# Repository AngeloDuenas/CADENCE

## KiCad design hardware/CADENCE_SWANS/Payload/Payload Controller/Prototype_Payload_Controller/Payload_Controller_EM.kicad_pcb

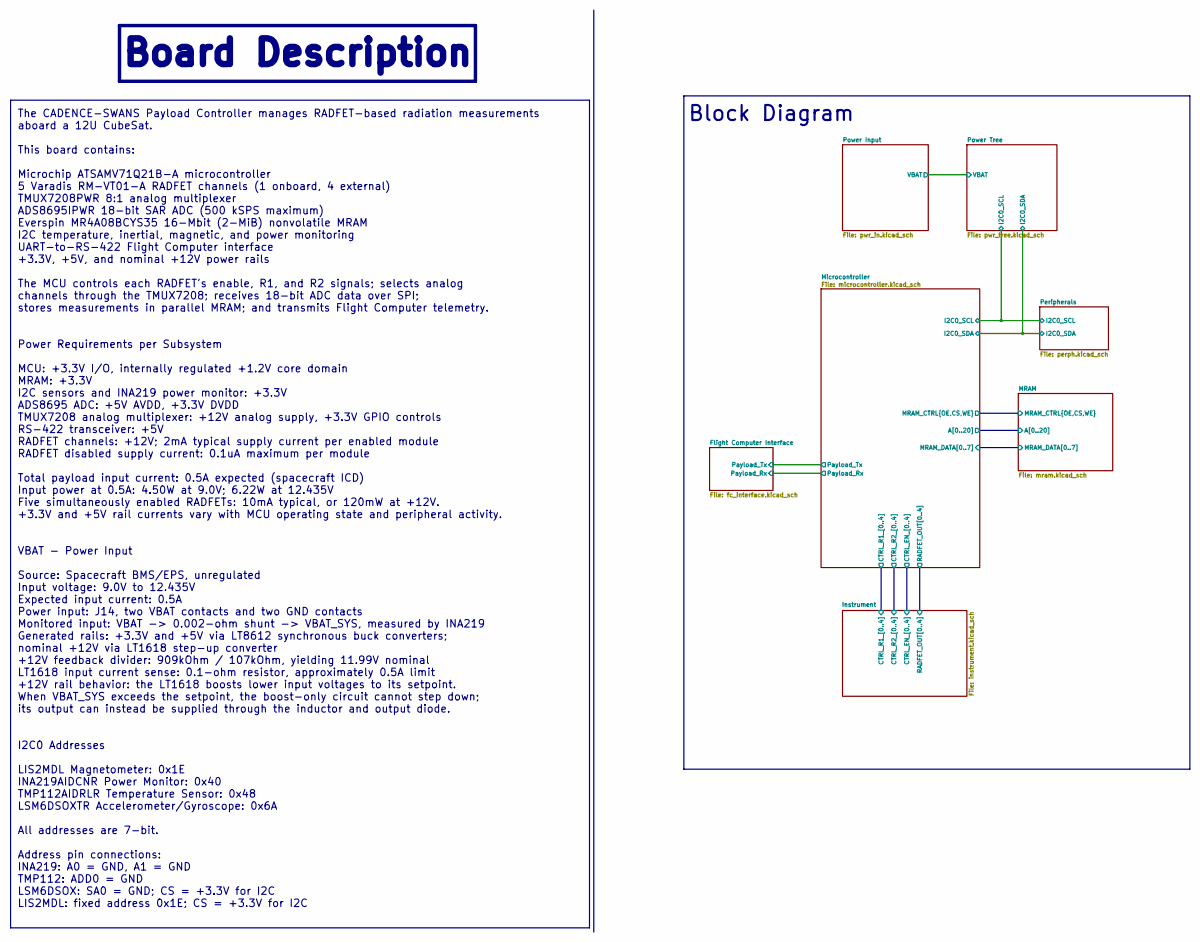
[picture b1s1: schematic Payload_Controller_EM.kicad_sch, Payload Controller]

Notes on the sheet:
Board Description
Block Diagram
The CADENCE-SWANS Payload Controller manages RADFET-based radiation measurements aboard a 12U CubeSat. This board contains: Microchip ATSAMV71Q21B-A microcontroller 5 Varadis RM-VT01-A RADFET channels (1 onboard, 4 external) TMUX7208PWR 8:1 analog multiplexer ADS8695IPWR 18-bit SAR ADC (500 kSPS ma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

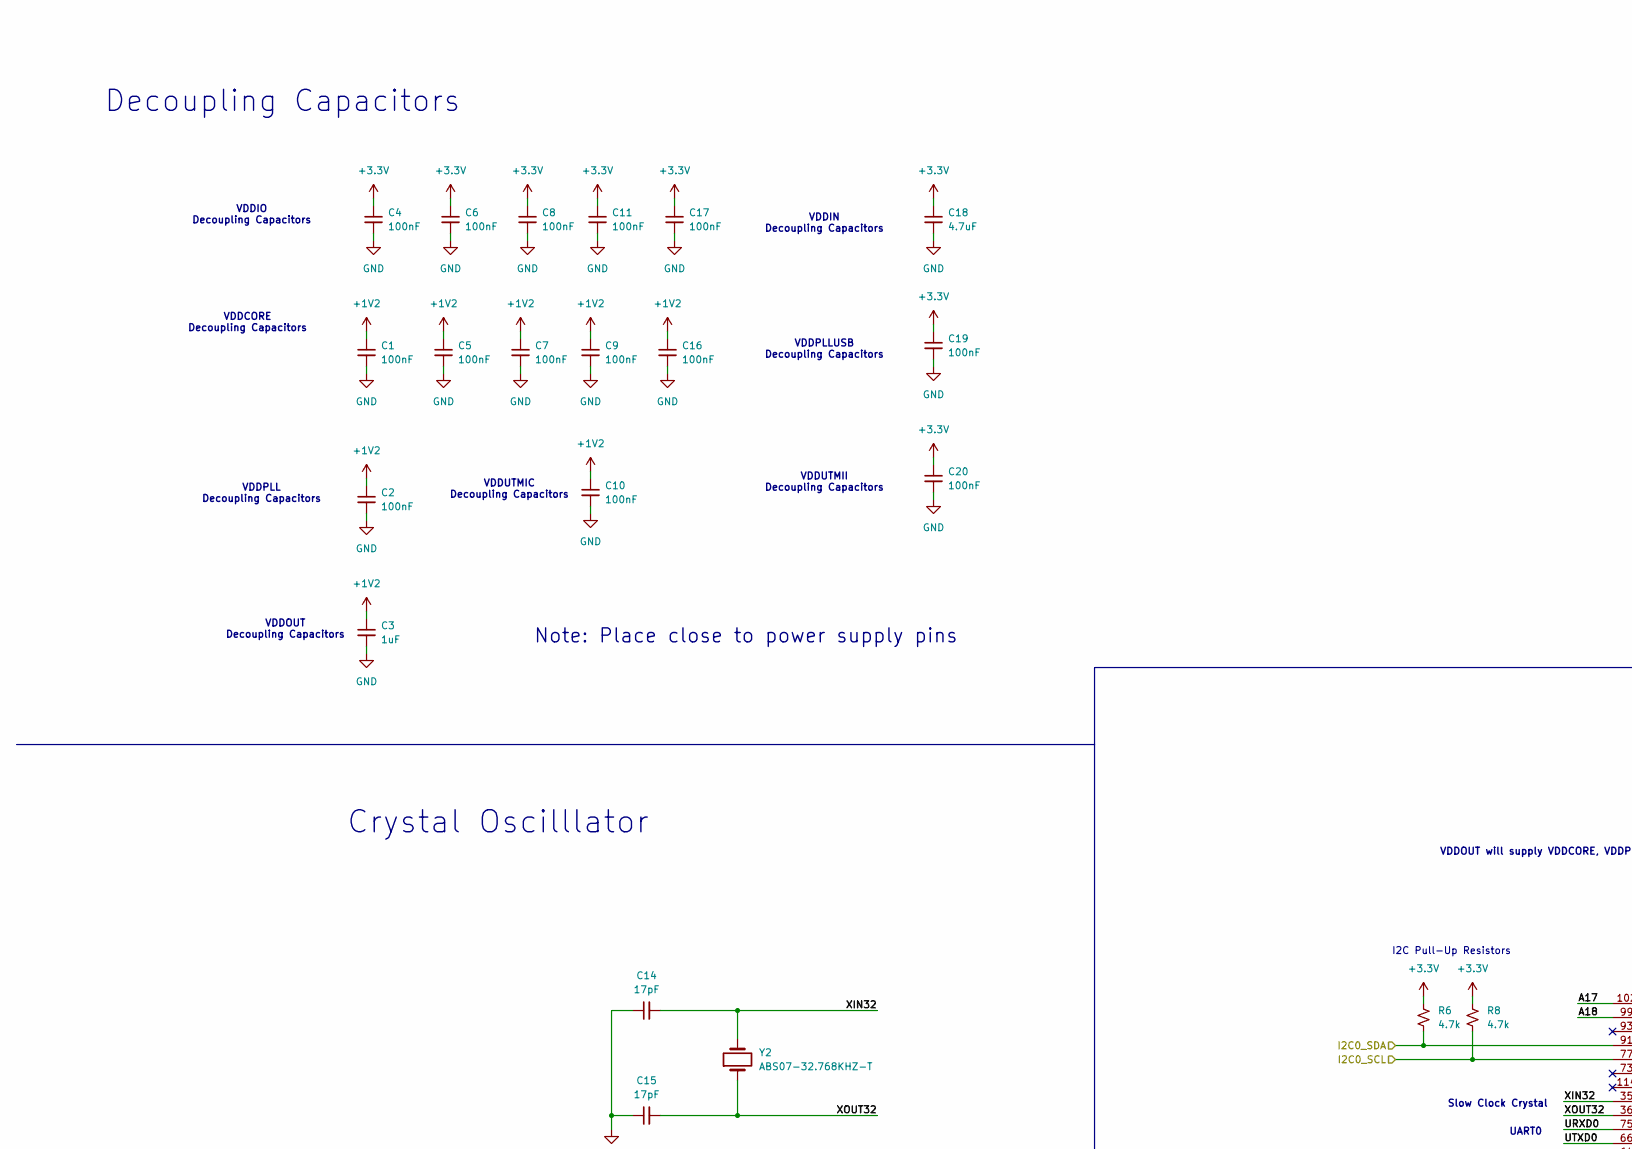
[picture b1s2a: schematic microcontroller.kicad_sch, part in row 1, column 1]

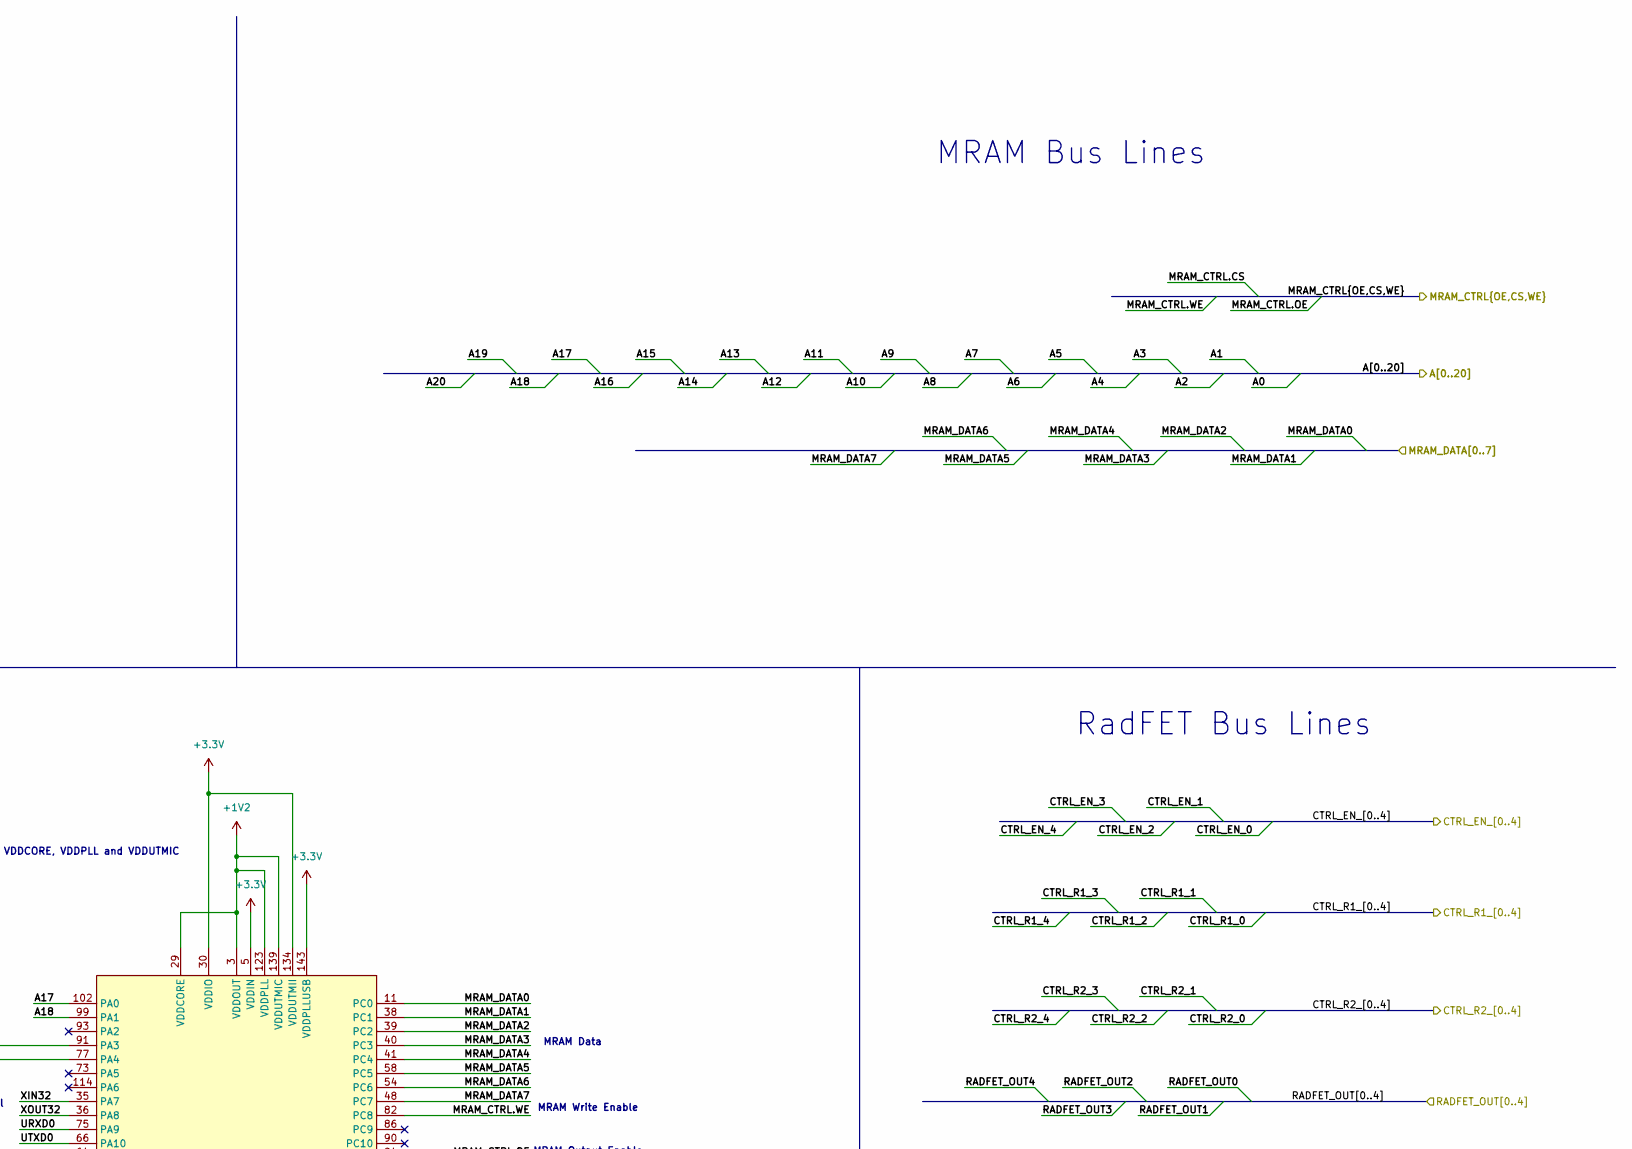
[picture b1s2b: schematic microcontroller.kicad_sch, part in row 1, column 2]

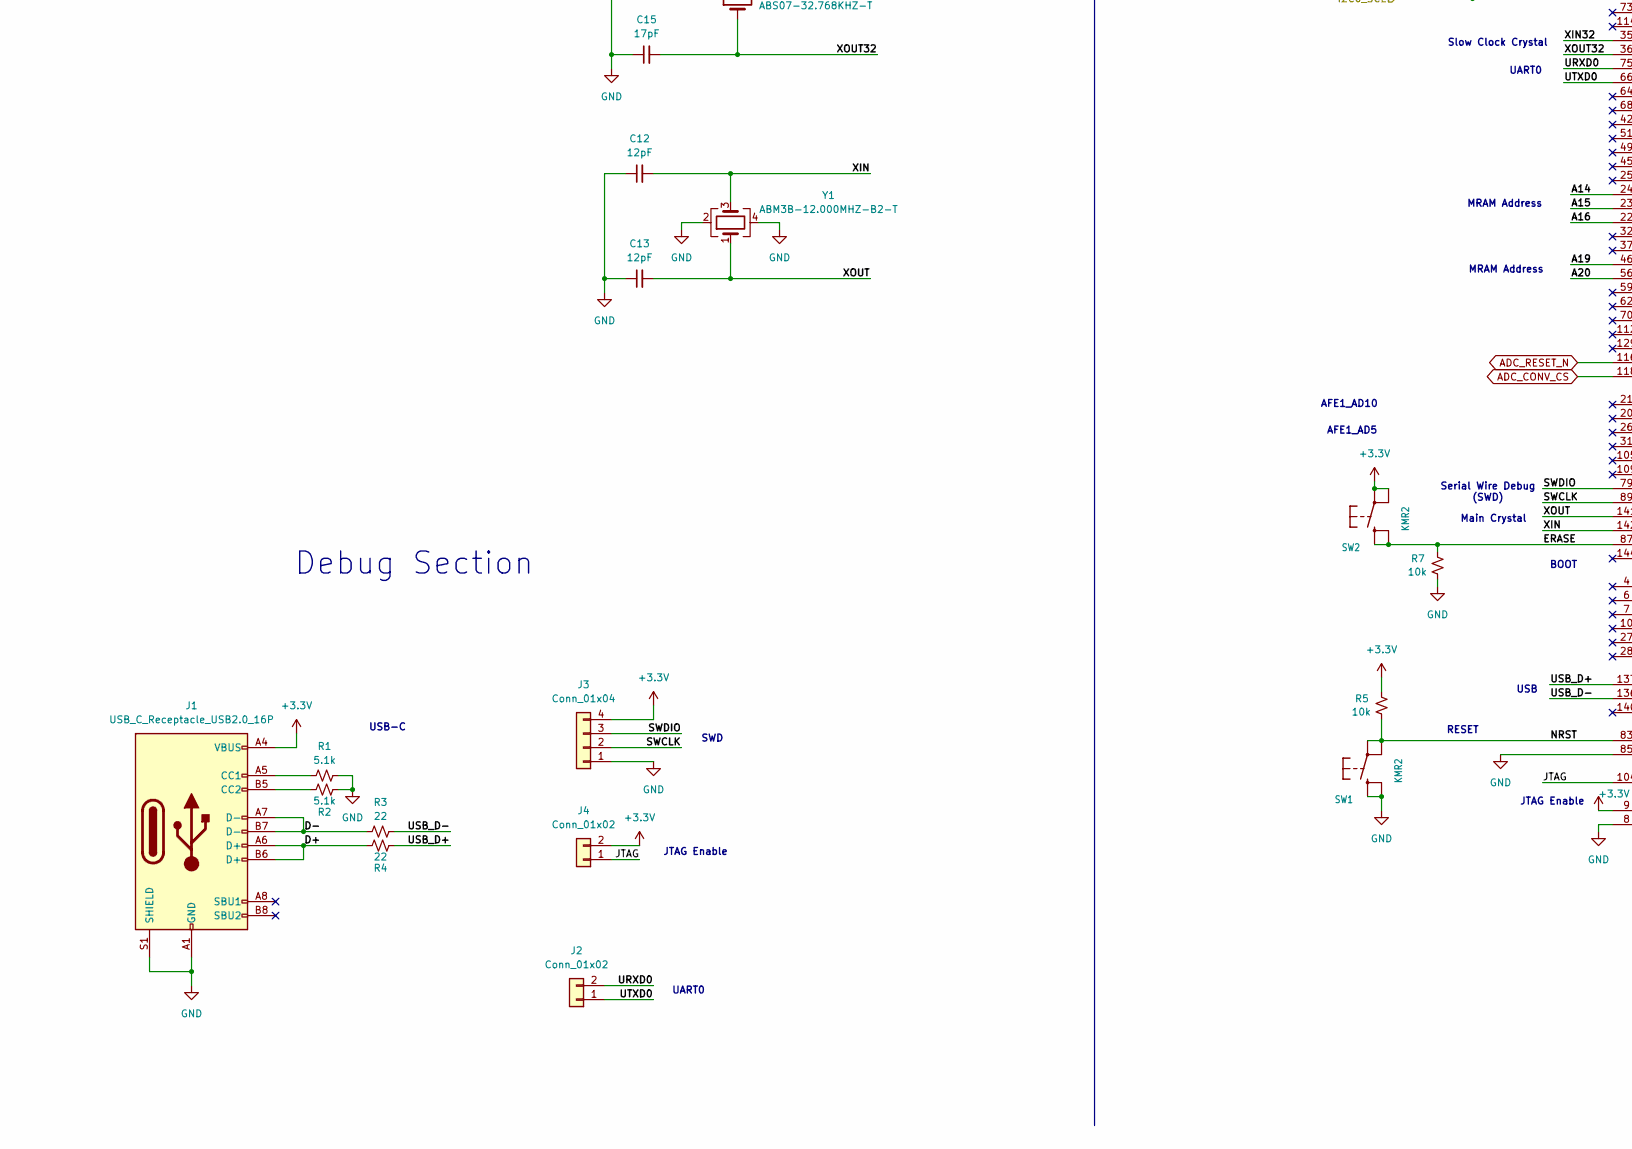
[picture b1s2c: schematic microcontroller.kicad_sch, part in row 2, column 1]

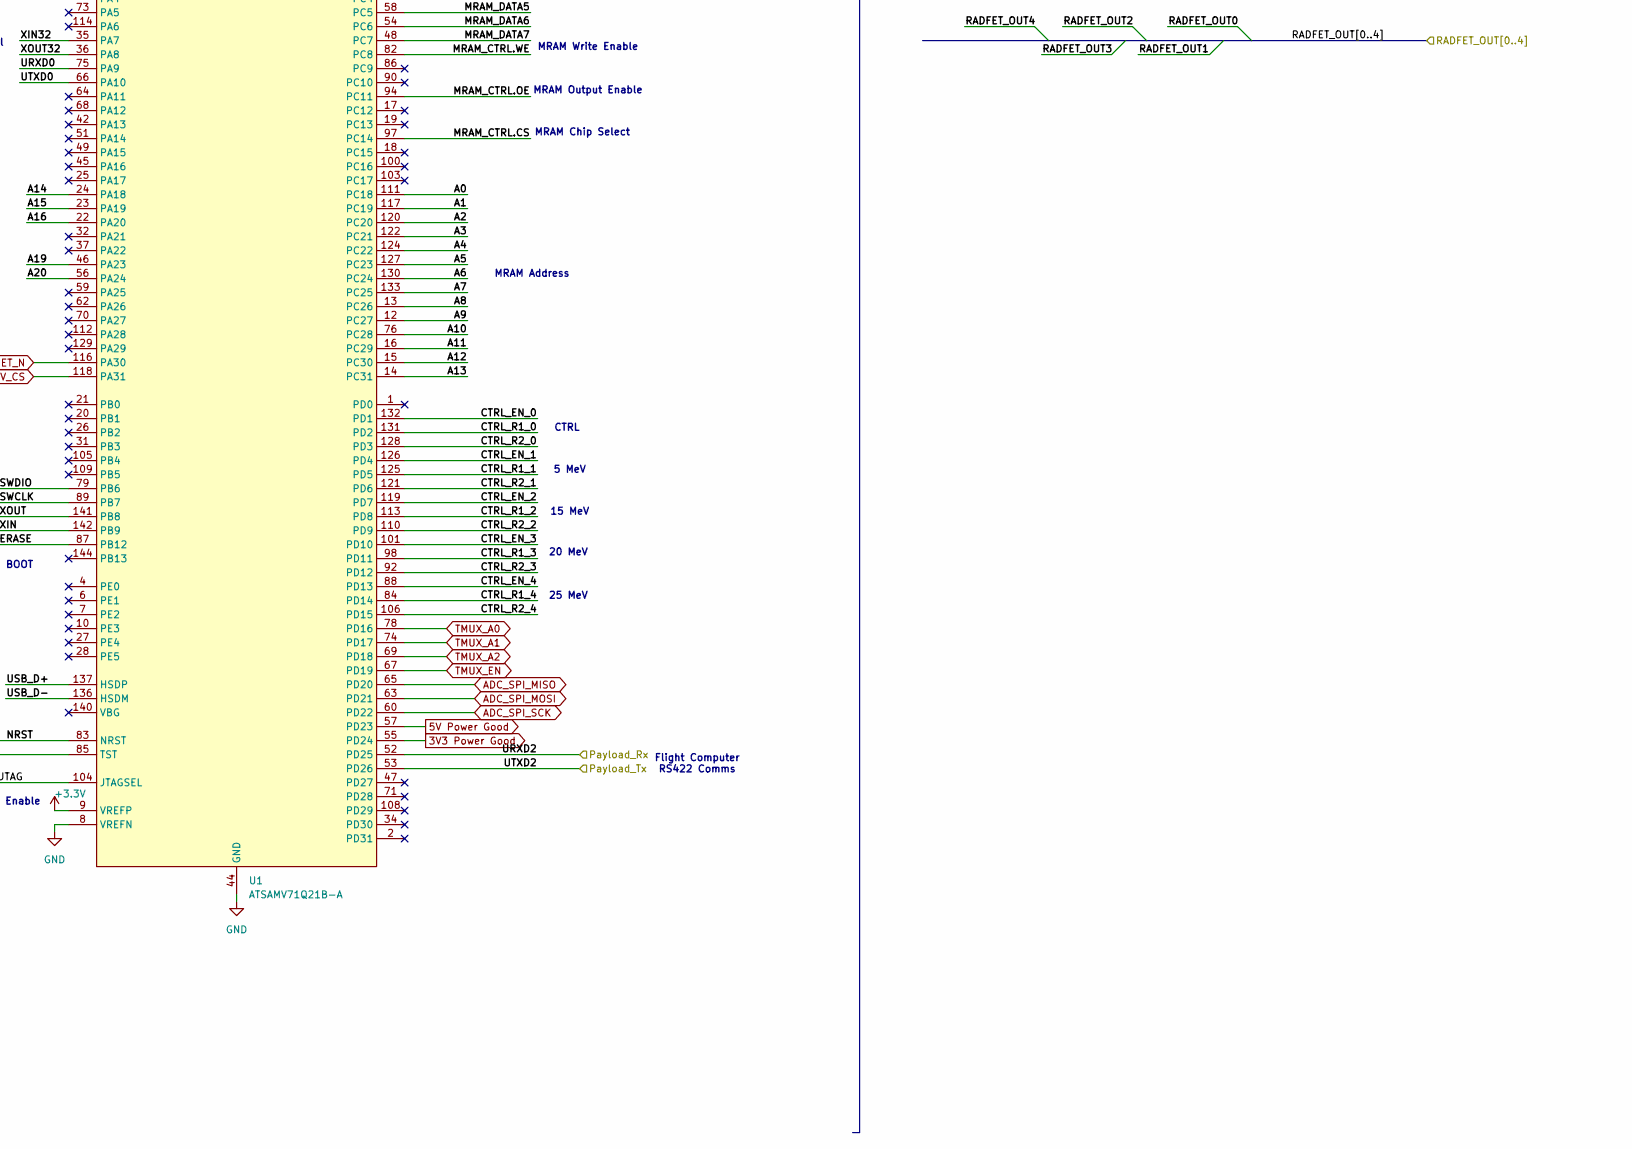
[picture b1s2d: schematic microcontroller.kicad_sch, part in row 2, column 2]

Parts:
C1, C2, C4, C5, C6, C7, C8, C9, C10, C11, C16, C17, C19, C20: 100nF; C_0402_1005Metric
C3: 1uF; C_0603_1608Metric
C12, C13: 12pF; C_0402_1005Metric
C14, C15: 17pF; C_0402_1005Metric
C18: 4.7uF; C_0603_1608Metric
J1: USB_C_Receptacle_USB2.0_16P; USB_C_Receptacle_HRO_TYPE-C-31-M-12
J2, J4: Conn_01x02; PinHeader_1x02_P2.54mm_Vertical
J3: Conn_01x04; PinHeader_1x04_P2.54mm_Vertical
R1, R2: 5.1k; R_0603_1608Metric
R3, R4: 22; R_0603_1608Metric
R5, R7: 10k; R_0603_1608Metric
R6, R8: 4.7k; R_0603_1608Metric
SW1, SW2: KMR2; BTN_KMR2_4.6X2.8
U1: ATSAMV71Q21B-A; LQFP-144_20x20mm_P0.5mm
Y1: ABM3B-12.000MHZ-B2-T; Crystal_SMD_3225-4Pin_3.2x2.5mm
Y2: ABS07-32.768KHZ-T; Crystal_SMD_3215-2Pin_3.2x1.5mm

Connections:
+1V2: C1.1, C2.1, C3.1, C5.1, C7.1, C9.1, C10.1, C16.1, U1.3 (VDDOUT), U1.29 (VDDCORE), U1.33 (VDDCORE), U1.50 (VDDCORE), U1.81 (VDDCORE), U1.107 (VDDCORE), U1.123 (VDDPLL), U1.139 (VDDUTMIC)
/Instrument/CTRL_EN_0: U1.132 (PD1); also elsewhere on the board
/Instrument/CTRL_EN_1: U1.126 (PD4); also elsewhere on the board
/Instrument/CTRL_EN_2: U1.119 (PD7); also elsewhere on the board
/Instrument/CTRL_EN_3: U1.101 (PD10); also elsewhere on the board
/Instrument/CTRL_EN_4: U1.88 (PD13); also elsewhere on the board
/Instrument/CTRL_R1_0: U1.131 (PD2); also elsewhere on the board
/Instrument/CTRL_R1_1: U1.125 (PD5); also elsewhere on the board
/Instrument/CTRL_R1_2: U1.113 (PD8); also elsewhere on the board
/Instrument/CTRL_R1_3: U1.98 (PD11); also elsewhere on the board
/Instrument/CTRL_R1_4: U1.84 (PD14); also elsewhere on the board
/Instrument/CTRL_R2_0: U1.128 (PD3); also elsewhere on the board
/Instrument/CTRL_R2_1: U1.121 (PD6); also elsewhere on the board
/Instrument/CTRL_R2_2: U1.110 (PD9); also elsewhere on the board
/Instrument/CTRL_R2_3: U1.92 (PD12); also elsewhere on the board
/Instrument/CTRL_R2_4: U1.106 (PD15); also elsewhere on the board
/MRAM/A0: U1.111 (PC18); also elsewhere on the board
/MRAM/A1: U1.117 (PC19); also elsewhere on the board
/MRAM/A2: U1.120 (PC20); also elsewhere on the board
/MRAM/A3: U1.122 (PC21); also elsewhere on the board
/MRAM/A4: U1.124 (PC22); also elsewhere on the board
/MRAM/A5: U1.127 (PC23); also elsewhere on the board
/MRAM/A6: U1.130 (PC24); also elsewhere on the board
/MRAM/A7: U1.133 (PC25); also elsewhere on the board
/MRAM/A8: U1.13 (PC26); also elsewhere on the board
/MRAM/A9: U1.12 (PC27); also elsewhere on the board
/MRAM/A10: U1.76 (PC28); also elsewhere on the board
/MRAM/A11: U1.16 (PC29); also elsewhere on the board
/MRAM/A12: U1.15 (PC30); also elsewhere on the board
/MRAM/A13: U1.14 (PC31); also elsewhere on the board
/MRAM/A14: U1.24 (PA18); also elsewhere on the board
/MRAM/A15: U1.23 (PA19); also elsewhere on the board
/MRAM/A16: U1.22 (PA20); also elsewhere on the board
/MRAM/A17: U1.102 (PA0); also elsewhere on the board
/MRAM/A18: U1.99 (PA1); also elsewhere on the board
/MRAM/A19: U1.46 (PA23); also elsewhere on the board
/MRAM/A20: U1.56 (PA24); also elsewhere on the board
/MRAM/MRAM_CTRL.CS: U1.97 (PC14); also elsewhere on the board
/MRAM/MRAM_CTRL.OE: U1.94 (PC11); also elsewhere on the board
/MRAM/MRAM_CTRL.WE: U1.82 (PC8); also elsewhere on the board
/MRAM/MRAM_DATA0: U1.11 (PC0); also elsewhere on the board
/MRAM/MRAM_DATA1: U1.38 (PC1); also elsewhere on the board
/MRAM/MRAM_DATA2: U1.39 (PC2); also elsewhere on the board
/MRAM/MRAM_DATA3: U1.40 (PC3); also elsewhere on the board
/MRAM/MRAM_DATA4: U1.41 (PC4); also elsewhere on the board
/MRAM/MRAM_DATA5: U1.58 (PC5); also elsewhere on the board
/MRAM/MRAM_DATA6: U1.54 (PC6); also elsewhere on the board
/MRAM/MRAM_DATA7: U1.48 (PC7); also elsewhere on the board
/Microcontroller/D+: J1.A6 (D+), J1.B6 (D+), R4.1
/Microcontroller/D-: J1.A7 (D-), J1.B7 (D-), R3.2
/Microcontroller/ERASE: R7.1, SW2.B (S), SW2.B' (S1), U1.87 (PB12)
/Microcontroller/JTAG: J4.1, U1.104 (JTAGSEL)
/Microcontroller/NRST: R5.2, SW1.A, SW1.A' (P1), U1.83 (NRST)
/Microcontroller/SWCLK: J3.2, U1.89 (PB7)
/Microcontroller/SWDIO: J3.3, U1.79 (PB6)
/Microcontroller/URXD0: J2.2, U1.75 (PA9)
/Microcontroller/URXD2: U1.52 (PD25); also elsewhere on the board
/Microcontroller/USB_D+: R4.2, U1.137 (HSDP)
/Microcontroller/USB_D-: R3.1, U1.136 (HSDM)
/Microcontroller/UTXD0: J2.1, U1.66 (PA10)
/Microcontroller/UTXD2: U1.53 (PD26); also elsewhere on the board
/Microcontroller/XIN: C12.2, U1.142 (PB9), Y1.3
/Microcontroller/XIN32: C14.2, U1.35 (PA7), Y2.2
/Microcontroller/XOUT: C13.2, U1.141 (PB8), Y1.1
/Microcontroller/XOUT32: C15.2, U1.36 (PA8), Y2.1
/Peripherals/I2C0_SCL: R8.2, U1.77 (PA4); also elsewhere on the board
/Peripherals/I2C0_SDA: R6.2, U1.91 (PA3); also elsewhere on the board
ADC_CONV_CS: U1.118 (PA31); also elsewhere on the board
ADC_RESET_N: U1.116 (PA30); also elsewhere on the board
ADC_SPI_MISO: U1.65 (PD20); also elsewhere on the board
ADC_SPI_MOSI: U1.63 (PD21); also elsewhere on the board
ADC_SPI_SCK: U1.60 (PD22); also elsewhere on the board
GND: C1.2, C2.2, C3.2, C4.2, C5.2, C6.2, C7.2, C8.2, C9.2, C10.2, C11.2, C12.1, C13.1, C14.1, C15.1, C16.2, C17.2, C18.2, C19.2, C20.2, J1.A1 (GND), J1.A12 (GND), J1.B1 (GND), J1.B12 (GND), J1.S1 (SHIELD), J3.1, R1.1, R2.2, R7.2, SW1.B (S), SW1.B' (S1), U1.8 (VREFN), U1.44 (GND), U1.61 (GND), U1.85 (TST), U1.95 (GND), U1.115 (GND), U1.135 (GND), U1.138 (GND), Y1.2, Y1.4; also elsewhere on the board
unnamed: J1.A5 (CC1), R1.2
unnamed: J1.B5 (CC2), R2.1
TMUX_A0: U1.78 (PD16); also elsewhere on the board
TMUX_A1: U1.74 (PD17); also elsewhere on the board
TMUX_A2: U1.69 (PD18); also elsewhere on the board
TMUX_EN: U1.67 (PD19); also elsewhere on the board

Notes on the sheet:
CTRL
VDDUTMIC Decoupling Capacitors
JTAG Enable
AFE1_AD10
MRAM Output Enable
Crystal Oscilllator
MRAM Chip Select
Note: Place close to power supply pins
20 MeV
VDDPLL Decoupling Capacitors
RESET
MRAM Write Enable
VDDIO Decoupling Capacitors
MRAM Address
RadFET Bus Lines
Debug Section
15 MeV
Flight Computer RS422 Comms
MRAM Data
VDDOUT Decoupling Capacitors
AFE1_AD5
VDDOUT will supply VDDCORE, VDDPLL and VDDUTMIC
25 MeV
Main Crystal
VDDUTMII Decoupling Capacitors
UART0
USB-C
Decoupling Capacitors
MRAM Bus Lines
I2C Pull-Up Resistors
BOOT
Slow Clock Crystal
VDDCORE Decoupling Capacitors
VDDIN Decoupling Capacitors
SWD
5 MeV
VDDPLLUSB Decoupling Capacitors
USB
Serial Wire Debug (SWD)

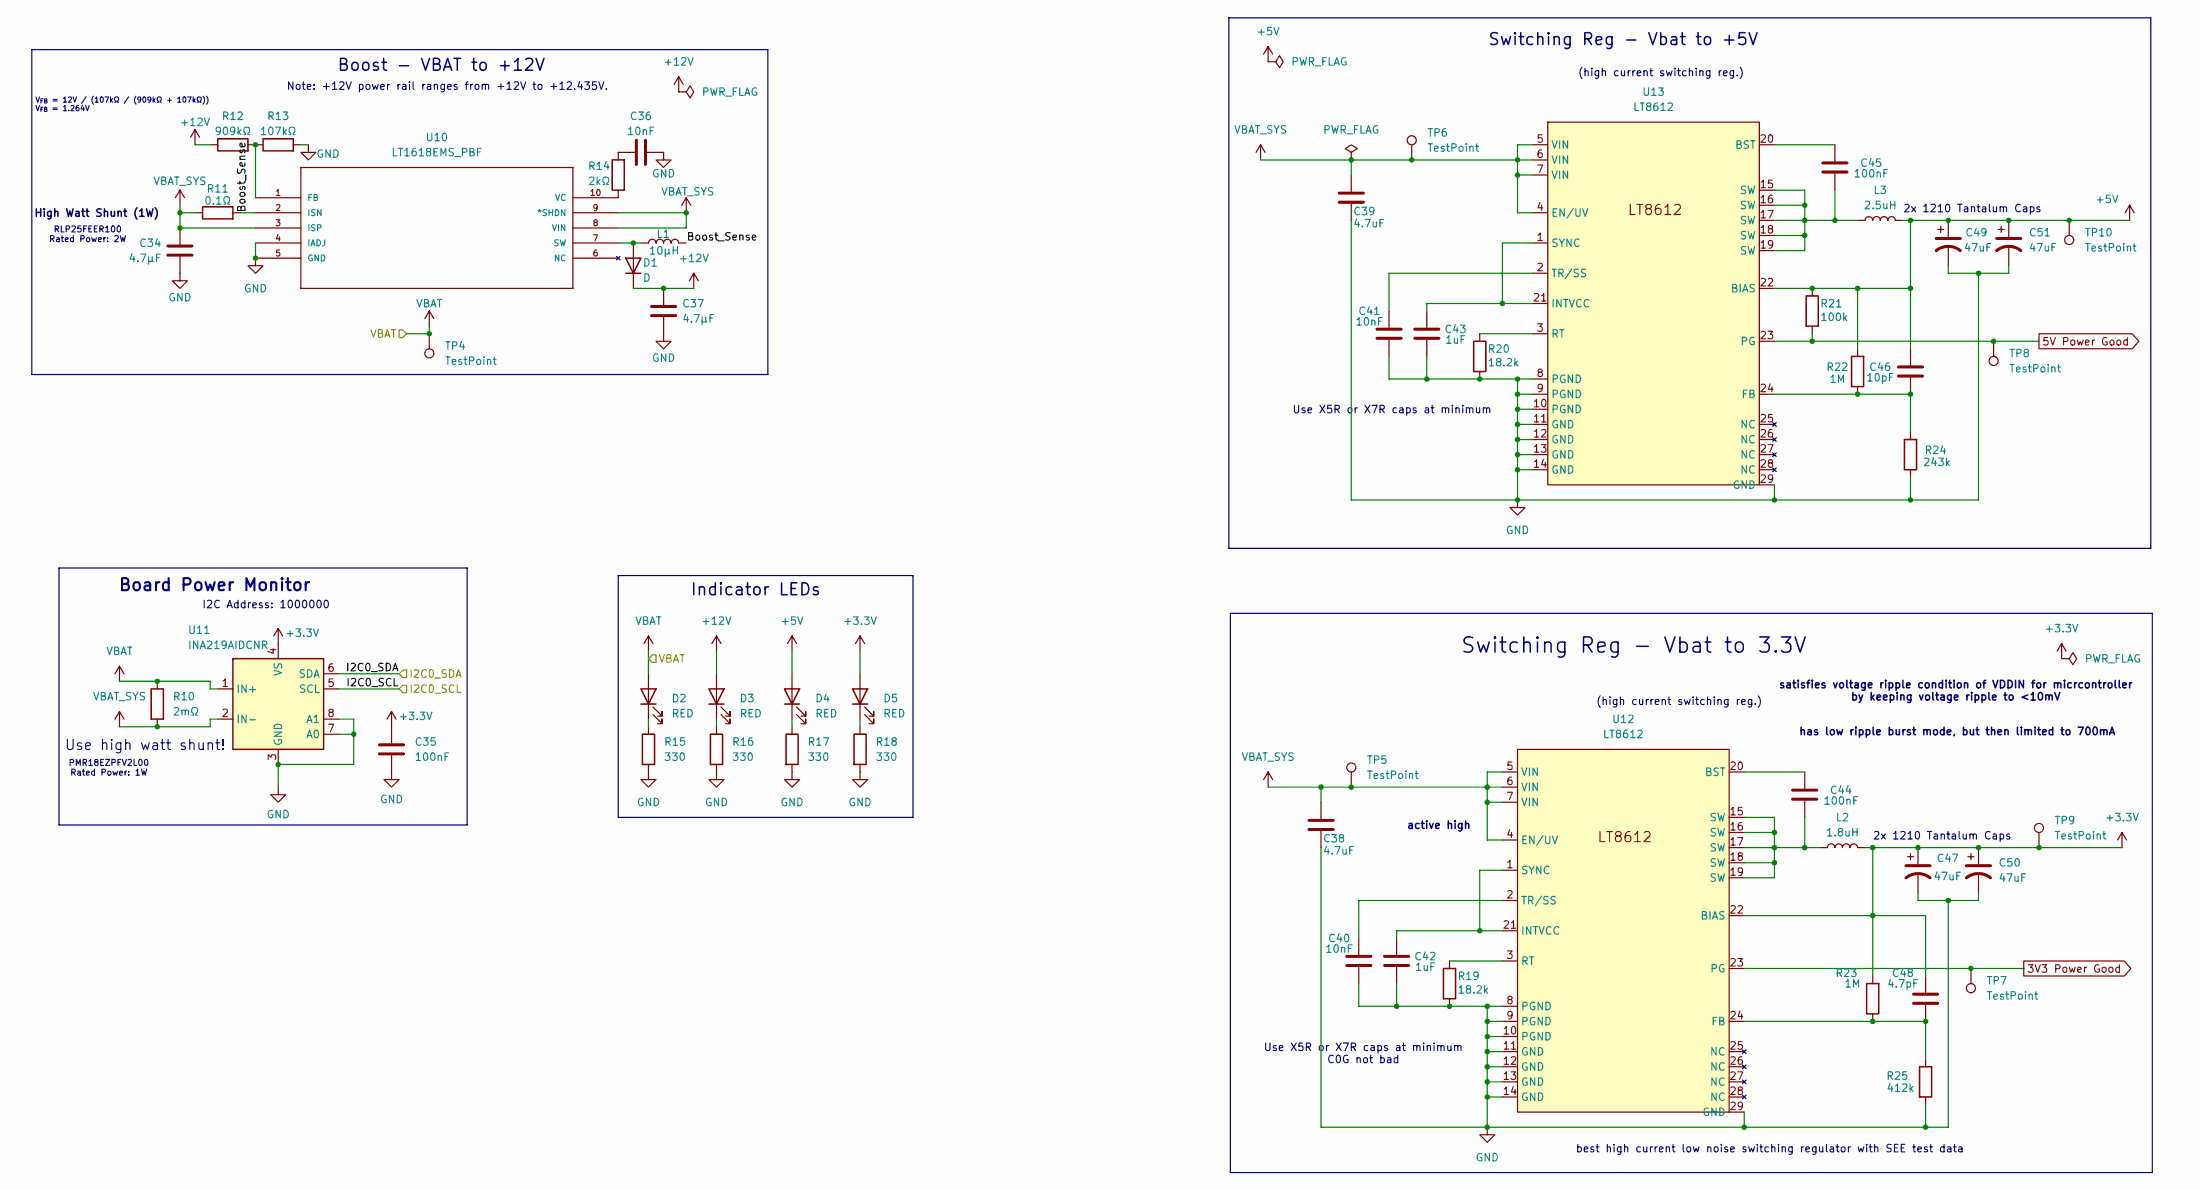
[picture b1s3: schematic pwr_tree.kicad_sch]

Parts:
C34, C37: 4.7µF; C_0805_2012Metric
C35, C44: 100nF; C_0603_1608Metric
C36, C41: 10nF; C_0402_1005Metric
C38, C39: 4.7uF; C_1206_3216Metric
C40: 10nF; C_0603_1608Metric
C42, C43: 1uF; C_0603_1608Metric
C45: 100nF; C_0402_1005Metric
C46: 10pF; C_0402_1005Metric
C47, C49, C50, C51: 47uF; C_1210_3225Metric
C48: 4.7pF; C_0603_1608Metric
D1: D; D_SMA
D2, D3, D4, D5: RED; LED_0603_1608Metric
L1: 10µH; L_Taiyo-Yuden_MD-5050
L2: 1.8uH; L_6.3x6.3_H3
L3: 2.5uH; L_6.3x6.3_H3
R10: 2mΩ; R_1206_3216Metric
R11: 0.1Ω; R_2512_6332Metric
R12: 909kΩ; R_0402_1005Metric
R13: 107kΩ; R_0402_1005Metric
R14: 2kΩ; R_0805_2012Metric
R15, R16, R17, R18: 330; R_0402_1005Metric
R19, R20: 18.2k; R_0402_1005Metric
R21: 100k; R_0402_1005Metric
R22: 1M; R_0603_1608Metric
R23: 1M; R_0402_1005Metric
R24: 243k; R_0402_1005Metric
R25: 412k; R_0402_1005Metric
TP4, TP5, TP6, TP7, TP8, TP9, TP10: TestPoint; TestPoint_Pad_1.0x1.0mm
U10: LT1618EMS_PBF; LT1618EMS#PBF; MPN LT1618EMS#PBF
U11: INA219AIDCNR; SOT-23-8
U12, U13: LT8612; QFN-28_UDE_LTI

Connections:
+5V: C46.2, C49.1, C51.1, D4.2 (A), L3.2, R21.1, R22.2, TP10.1, U13.22 (BIAS); also elsewhere on the board
+12V: C37.1, D1.1 (K), D3.2 (A), R12.1; also elsewhere on the board
/Peripherals/I2C0_SCL: U11.5 (SCL); also elsewhere on the board
/Peripherals/I2C0_SDA: U11.6 (SDA); also elsewhere on the board
/Power Tree/Boost_Sense: L1.2, R11.2, U10.2 (ISN)
GND: C34.2, C35.2, C36.1, C37.2, C38.2, C39.2, C40.1, C41.1, C42.1, C43.1, C47.2, C49.2, C50.2, C51.2, R13.2, R15.2, R16.2, R17.2, R18.2, R19.2, R20.2, R24.1, R25.2, U10.4 (IADJ), U10.5 (GND), U11.3 (GND), U11.7 (A0), U11.8 (A1), U12.8 (PGND), U12.9 (PGND), U12.10 (PGND), U12.11 (GND), U12.12 (GND), U12.13 (GND), U12.14 (GND), U12.29 (GND), U13.8 (PGND), U13.9 (PGND), U13.10 (PGND), U13.11 (GND), U13.12 (GND), U13.13 (GND), U13.14 (GND), U13.29 (GND); also elsewhere on the board
unnamed: C36.2, R14.2
unnamed: C44.1, L2.1, U12.15 (SW), U12.16 (SW), U12.17 (SW), U12.18 (SW), U12.19 (SW)
unnamed: C45.1, L3.1, U13.15 (SW), U13.16 (SW), U13.17 (SW), U13.18 (SW), U13.19 (SW)
unnamed: D1.2 (A), L1.1, U10.7 (SW)
unnamed: D2.1 (K), R15.1
unnamed: D3.1 (K), R16.1
unnamed: D4.1 (K), R17.1
unnamed: D5.1 (K), R18.1
unnamed: R12.2, R13.1, U10.1 (FB)
unnamed: R14.1, U10.10 (VC)
unnamed: C44.2, U12.20 (BST)
unnamed: C48.1, R23.1, R25.1, U12.24 (FB)
unnamed: C42.2, U12.1 (SYNC), U12.21 (INTVCC)
unnamed: R19.1, U12.3 (RT)
unnamed: C40.2, U12.2 (TR/SS)
unnamed: C45.2, U13.20 (BST)
unnamed: C46.1, R22.1, R24.2, U13.24 (FB)
unnamed: C43.2, U13.1 (SYNC), U13.21 (INTVCC)
unnamed: R20.1, U13.3 (RT)
unnamed: C41.2, U13.2 (TR/SS)
VBAT: D2.2 (A), R10.1, TP4.1, U11.1 (IN+); also elsewhere on the board

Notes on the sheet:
(high current switching reg.)
I2C Address: 1000000
best high current low noise switching regulator with SEE test data
active high
Note: +12V power rail ranges from +12V to +12.435V.
satisfies voltage ripple condition of VDDIN for micrcontroller by keeping voltage ripple to <10mV
has low ripple burst mode, but then limited to 700mA
Board Power Monitor
Use X5R or X7R caps at minimum
2x 1210 Tantalum Caps
Use high watt shunt!
RLP25FEER100 Rated Power: 2W
Use X5R or X7R caps at minimum C0G not bad
Boost - VBAT to +12V
Indicator LEDs
V_{FB} = 12V / (107kΩ / (909kΩ + 107kΩ)) V_{FB} = 1.264V
Switching Reg - Vbat to +5V
PMR18EZPFV2L00 Rated Power: 1W
High Watt Shunt (1W)
Switching Reg - Vbat to 3.3V

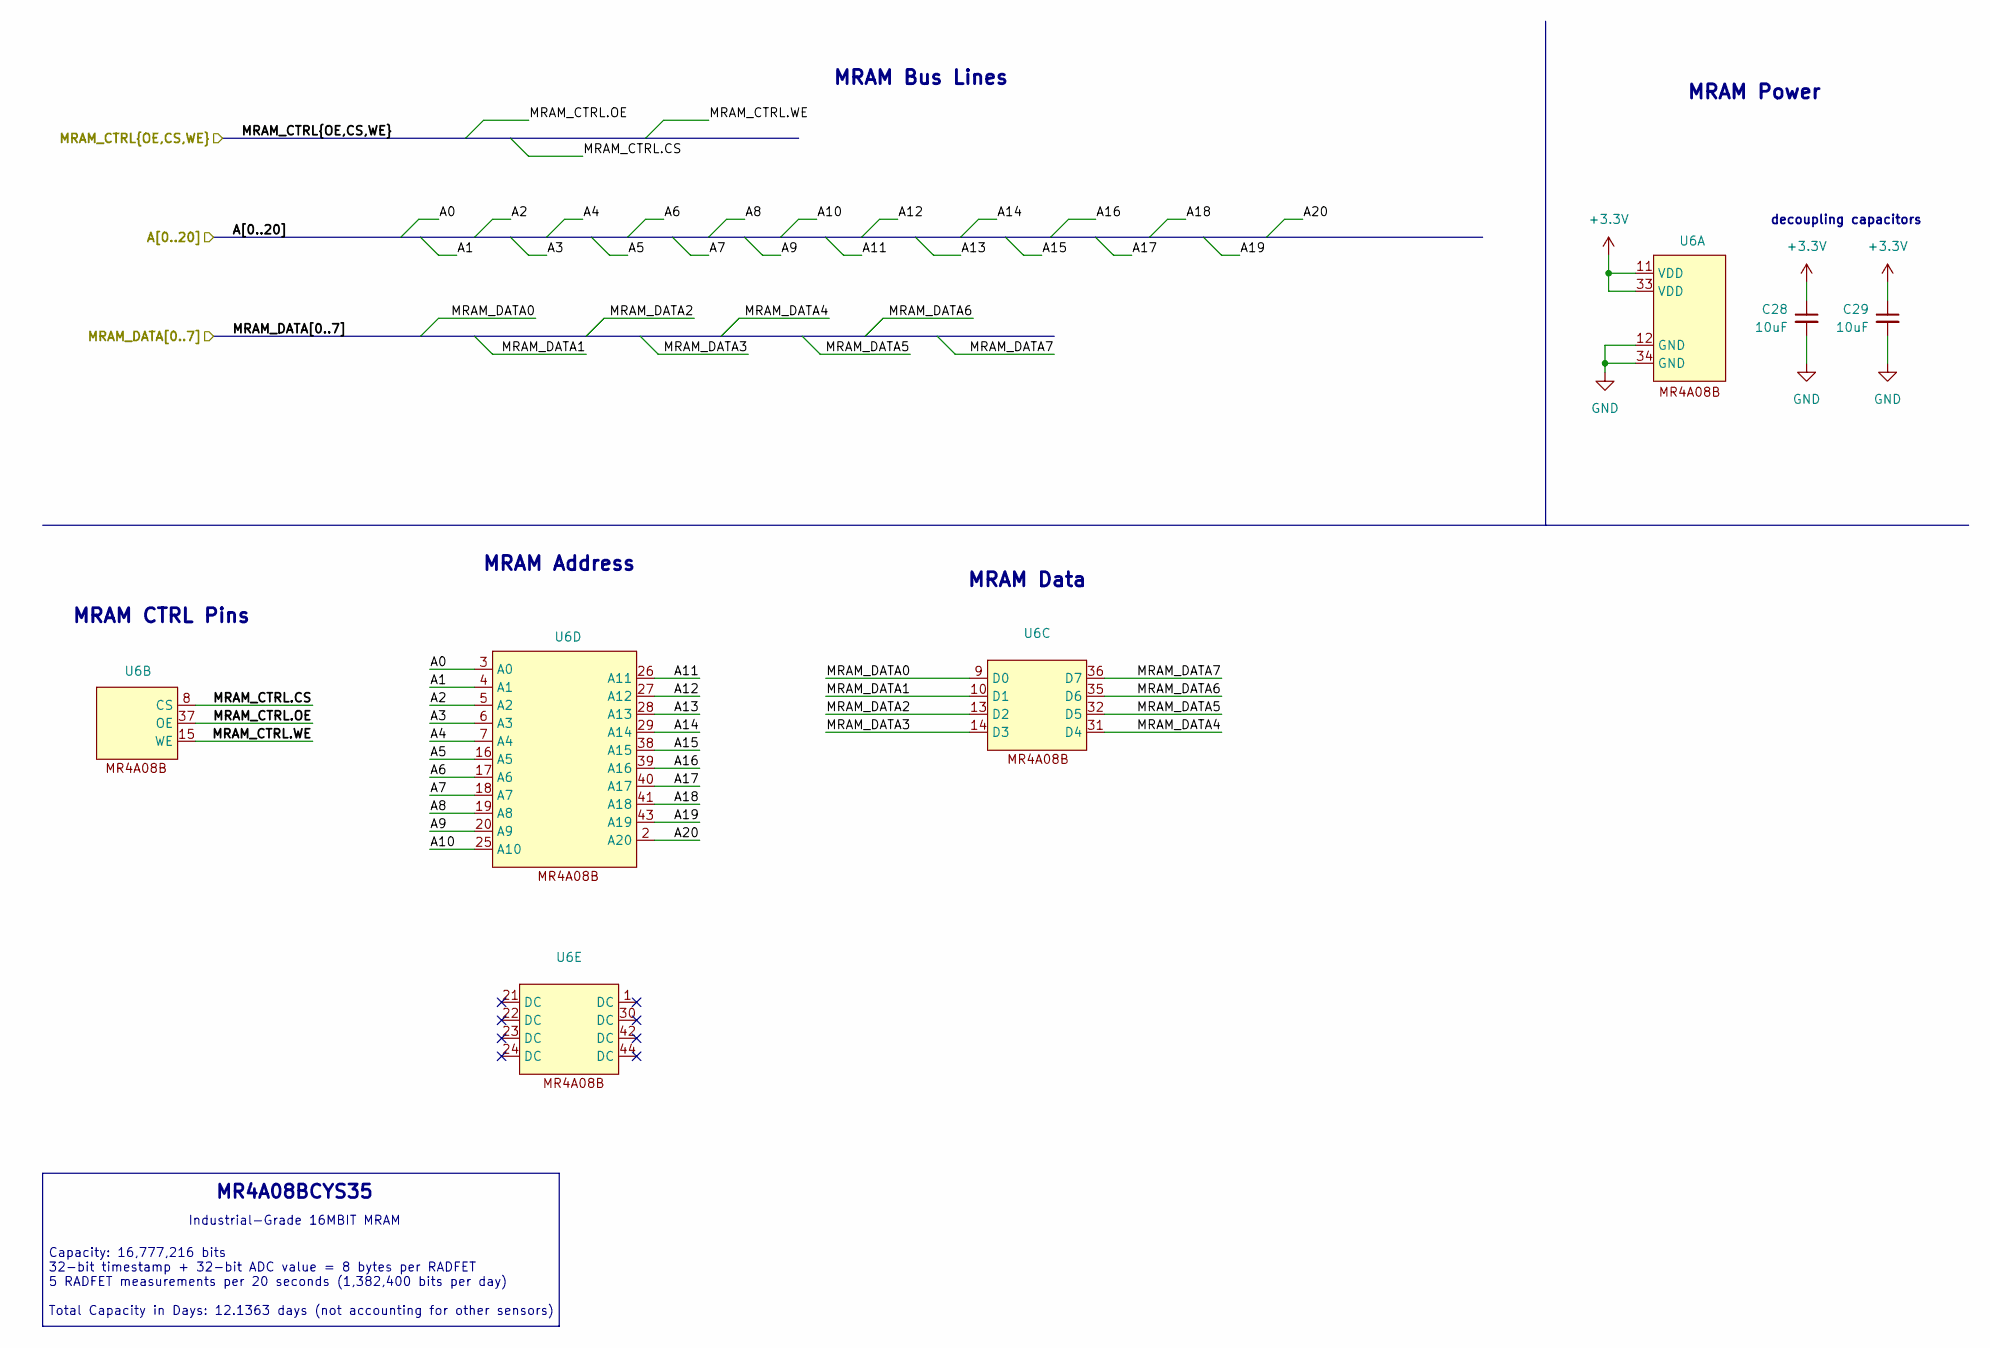
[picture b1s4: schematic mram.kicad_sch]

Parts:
C28, C29: 10uF; C_0603_1608Metric
U6: TSOP-II-44_10.16x18.41mm_P0.8mm

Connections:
/MRAM/A0: U6.3 (A0); also elsewhere on the board
/MRAM/A1: U6.4 (A1); also elsewhere on the board
/MRAM/A2: U6.5 (A2); also elsewhere on the board
/MRAM/A3: U6.6 (A3); also elsewhere on the board
/MRAM/A4: U6.7 (A4); also elsewhere on the board
/MRAM/A5: U6.16 (A5); also elsewhere on the board
/MRAM/A6: U6.17 (A6); also elsewhere on the board
/MRAM/A7: U6.18 (A7); also elsewhere on the board
/MRAM/A8: U6.19 (A8); also elsewhere on the board
/MRAM/A9: U6.20 (A9); also elsewhere on the board
/MRAM/A10: U6.25 (A10); also elsewhere on the board
/MRAM/A11: U6.26 (A11); also elsewhere on the board
/MRAM/A12: U6.27 (A12); also elsewhere on the board
/MRAM/A13: U6.28 (A13); also elsewhere on the board
/MRAM/A14: U6.29 (A14); also elsewhere on the board
/MRAM/A15: U6.38 (A15); also elsewhere on the board
/MRAM/A16: U6.39 (A16); also elsewhere on the board
/MRAM/A17: U6.40 (A17); also elsewhere on the board
/MRAM/A18: U6.41 (A18); also elsewhere on the board
/MRAM/A19: U6.43 (A19); also elsewhere on the board
/MRAM/A20: U6.2 (A20); also elsewhere on the board
/MRAM/MRAM_CTRL.CS: U6.8 (CS); also elsewhere on the board
/MRAM/MRAM_CTRL.OE: U6.37 (OE); also elsewhere on the board
/MRAM/MRAM_CTRL.WE: U6.15 (WE); also elsewhere on the board
/MRAM/MRAM_DATA0: U6.9 (D0); also elsewhere on the board
/MRAM/MRAM_DATA1: U6.10 (D1); also elsewhere on the board
/MRAM/MRAM_DATA2: U6.13 (D2); also elsewhere on the board
/MRAM/MRAM_DATA3: U6.14 (D3); also elsewhere on the board
/MRAM/MRAM_DATA4: U6.31 (D4); also elsewhere on the board
/MRAM/MRAM_DATA5: U6.32 (D5); also elsewhere on the board
/MRAM/MRAM_DATA6: U6.35 (D6); also elsewhere on the board
/MRAM/MRAM_DATA7: U6.36 (D7); also elsewhere on the board
GND: C28.2, C29.2, U6.12 (GND), U6.34 (GND); also elsewhere on the board

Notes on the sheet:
MRAM Power
Capacity: 16,777,216 bits 32-bit timestamp + 32-bit ADC value = 8 bytes per RADFET 5 RADFET measurements per 20 seconds (1,382,400 bits per day) Total Capacity in Days: 12.1363 days (not accounting for other sensors)
MR4A08BCYS35
MRAM Bus Lines
decoupling capacitors
MRAM Data
MRAM Address
MRAM CTRL Pins
Industrial-Grade 16MBIT MRAM

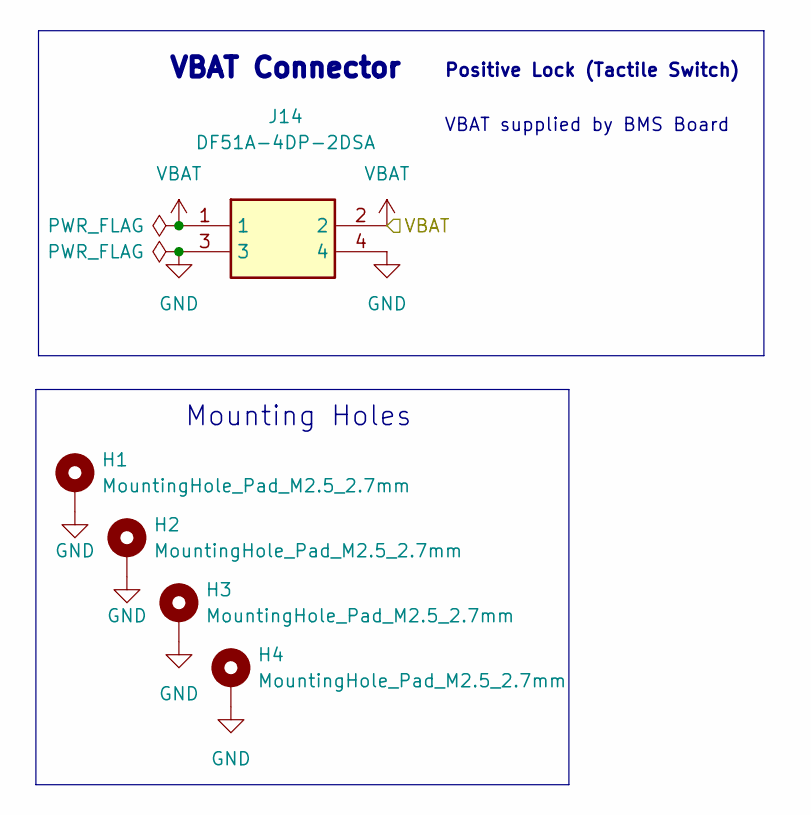
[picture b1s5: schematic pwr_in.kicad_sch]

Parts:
H1, H2, H3, H4: MountingHole_Pad_M2.5_2.7mm; MountingHole_2.7mm_M2.5_DIN965_Pad
J14: DF51A-4DP-2DSA; SHDR4W60P200X200_2X2_1110X730X870P; Manufacturer_Part_Number DF51A-4DP-2DSA; Mouser Part Number 798-DF51A-4DP-2DSA

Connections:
GND: H1.1 (MP), H2.1 (MP), H3.1 (MP), H4.1 (MP), J14.3, J14.4; also elsewhere on the board
VBAT: J14.1, J14.2; also elsewhere on the board

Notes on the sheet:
VBAT Connector
Positive Lock (Tactile Switch)
Mounting Holes
VBAT supplied by BMS Board
